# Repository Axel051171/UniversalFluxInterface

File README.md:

<!-- boardrepo-badge:v1 -->

<!-- /boardrepo-badge:v1 -->

# UFI – Universal Flux Interface (Headless)

Flux-Lese-/Schreibgerät für Disketten: STM32H723 (550 MHz) misst jede Flusswechsel-Zeit mit
275 MHz (3,6 ns) und streamt sie per USB an den PC. Kein Raspberry Pi, kein Betriebssystem auf
dem Gerät – das frühere CM5-/Modul-Konzept ist aufgegeben (steht in der Git-Historie).

| | |
|---|---|
| MCU | STM32H723ZGT6, 550 MHz |
| Auflösung | 275 MHz Timer-Capture (3,6 ns), Index auf derselben Zeitbasis |
| Puffer | 8 MB QSPI-PSRAM (Ringpuffer beim Streamen, bis 200 Umdrehungen) |
| USB | USB-C, Full Speed, Datenstrom ~2 Byte je Flusswechsel, sendet während die Diskette dreht |
| Laufwerke | 34-pol PC/Shugart (DENSITY, DRATE, bis 4 Laufwerke), Amiga DB23 (Header, 2 Laufwerke), Apple Disk II (20-pol, 2 Laufwerke), Commodore IEC (1541) |
| Schreiben | Timer + DMA, Precompensation, Verify; Schreibsperre in Hardware (Frontschalter SCHREIBEN + Firmware-Freigabe) |
| Platine v1.0 | 110 × 97 mm, 6 Lagen, für ein geschlossenes Gehäuse (von außen nur USB-C und LAN): eFuses für 5 V/12 V der Laufwerke mit Strommessung, MOSFET-Bustreiber, 4 GB SD-NAND, TCXO, RTC mit CR2032, SHT40, W5500-LAN, Apple-Disk-II- und Mac-3,5"-Port, Sync-Sensor-Eingang, Front-Header J12 |
| Ohne PC | Taster: ganze Diskette als SCP auf den internen Speicher (mit Qualitätsbericht) oder Disk-zu-Disk-Kopie, danach als USB-Laufwerk am PC abholen |
| Greaseweazle-kompatibel | `UFI.CFG protocol=gw`: die Greaseweazle-Werkzeuge (`gw read`, `gw write`, …) erkennen das Board direkt |
| USB-Floppy | Betriebsart-Schalter: PC-Disketten (360K–2,88 MB, DMF) erscheinen am PC als normales USB-Diskettenlaufwerk, ohne Treiber; Atari ST, Commodore 1581 und Amiga 880K als Block-Laufwerk (Sektorabbild wie ST/D81/ADF) |

## Aufbau des Repos

| Ordner | Inhalt |
|---|---|
| [`kicad/UFI_Headless/`](kicad/UFI_Headless/README.md) | Schaltplan, Layout, Fertigungsdaten (`fertigung/`), Build- und ECO-Skripte |
| [`kicad/C64_PSU_Guard/`](kicad/C64_PSU_Guard/README.md) | Eigenständige Schutzplatine: 5 V / 12 V aus einem PC-Netzteil für ein 1541-II / 1581 (eFuse, Verpolschutz, Fehler-LEDs), JLC-Fertigungsdaten |
| [`firmware/`](firmware/) | STM32H723-Firmware (CMake, STM32Cube HAL) |
| [`software/ufi_host/`](software/ufi_host/README.md) | Python-Host (`ufi`): Lesen/Schreiben, SCP-Export, Protokollbeschreibung |
| [`docs/`](docs/README.md) | USB-Protokoll, Umsetzungsstand und Nachweise der Firmware, Speicheraufteilung, Abnahmepläne, Vergleiche mit fremder Floppy-Firmware, Amiga-DB23-Adapterkabel |

## Firmware bauen

```bash
cmake -S firmware -B firmware/build -G Ninja
cmake --build firmware/build        # -> ufi_firmware.bin
```

Erwartet arm-none-eabi-gcc und STM32Cube H7 V1.11.0 unter `~/STM32Cube/Repository/STM32Cube_FW_H7_V1.11.0`
(Pfad in `firmware/CMakeLists.txt`).

Flashen per SWD oder USB-DFU (Taster A beim Einschalten halten bzw. `ufi bootloader`).

## Prüfen ohne Hardware

```bash
pip install -r requirements-test.txt     # pytest, pyserial, py65 (festgelegte Versionen)
python firmware/tests/check_all.py       # native Tests, Firmware-Regressionen, Host-Tests, 6502-Laufwerkscode
```

Braucht clang oder gcc. Die externen Referenzkorpora werden ohne Download übersprungen
(`python firmware/tests/test_flux_corpus.py --download`, ebenso `test_gcr_corpus.py`,
`test_hfe_v3_reference.py`); mit `--require-corpora` schlägt der Lauf ohne sie fehl.
Ergebnis in `firmware/tests/build/offline_gate.json`. Weitere Schritte der CI:
`firmware/tools/check_static.py` (Clang-Analyse, 34 Module, HAL-gebundene gegen `firmware/tests/hal_stub/`),
`firmware/tests/run_fuzz.py` (LibFuzzer: Dateiparser, der komplette v2-Dispatcher, das Greaseweazle-Protokoll
das SD-Modul mit Bildladern, Dump-Writern und UFI.CFG über ein In-Memory-FatFs und die Laufwerkssteuerung
gegen ein Kopfmodell mit TRK00-Sensor, alles hinter erzeugten Treiber-Stubs, `--target v2|gw|sd|drive`).
`python firmware/tests/coverage.py` misst mit clang/llvm-cov, welche Zeilen und Zweige der nativ
gebauten Firmware-Module die Tests erreichen (`firmware/tests/build/coverage.txt`, `cov/html/`).

## Status

Platine v1.0 ist zur Fertigung freigegeben (Tag `hw-v1.0`: ERC 0/0, DRC 0/0/0 mit Schaltplan-Parität, Lastpfade geprüft, JLC-Daten in `kicad/UFI_Headless/fertigung/`) – [Freigabebericht](kicad/UFI_Headless/docs/Freigabe_v1.0.md), [Bestell-Anleitung JLC](kicad/UFI_Headless/docs/Bestellung_JLC.md). Die LAN-Firmware fehlt noch; bis dahin bleibt der W5500 im Reset.
Firmware 1.18-dev: Umfang und Nachweise in [docs/Implementation_Status.md](docs/Implementation_Status.md) und
[docs/Firmware_Erweiterungen_2026-10-16.md](docs/Firmware_Erweiterungen_2026-10-16.md), Schnittstelle in [docs/USB_Protokoll.md](docs/USB_Protokoll.md).
Hardware und Firmware sind noch nicht am echten Gerät getestet – Ablauf für den Prototyp: [Inbetriebnahme-Checkliste](kicad/UFI_Headless/docs/Inbetriebnahme.md),
Schreibpfad: [Abnahme](docs/Abnahme_Schreibpfad.md).

Lizenz: siehe [LICENSE](LICENSE).

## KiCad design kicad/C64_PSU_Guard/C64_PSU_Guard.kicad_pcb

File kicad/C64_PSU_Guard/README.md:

# C64 PSU Guard – geschützte 5 V / 12 V für ein 1541-II / 1581 aus einem PC-Netzteil

Status: **Schaltplan + Layout v0.2** (2026-10-26, Review vom 2026-10-24 umgesetzt), ERC 0/0, DRC 0/0/0, Lastpfade mit `check_routing.py` gemessen (2 Lagen, 58 × 44 mm, JLCPCB-Bestückung), **noch nicht gebaut**.

Änderungen v0.1 → v0.2: J1 und J3 verpolsichere JST-XH-Stecker (B4B-XH-A) statt Stiftleisten, D6 SMAJ13A (unidirektional) statt SMAJ15CA, 100k-Pull-ups R20/R21 an FLT5/FLT12, Lastpfade durchgehend 1,0 mm (v0.1: Zwischenknoten V5_P/V12_P nur 0,25 mm, weil das Netzklassen-Muster den Blattpräfix `/` nicht traf), J3 1:1 auf UFI v1.0 J20 GUARD.

Eigenständige Platine, unabhängig vom UFI-Board. Sie sitzt zwischen dem internen PC-Netzteil des Geräts und dem 4-poligen DIN-Stromanschluss des Commodore-Laufwerks (Original-Netzteil DV-5128UP: 5 V 700 mA, 12 V 500 mA) und ersetzt dessen Schutzfunktion. Ein PC-Netzteil liefert auf beiden Schienen viele Ampere, ohne Begrenzung würde ein Kurzschluss im Laufwerk das dünne DIN-Kabel und die Laufwerksplatine beschädigen.

Klemme J2 mit Ersatzmodell (Phoenix MKDS, gleiche Bauform) zur Kontrolle der Drahtöffnungen: `docs/j2_terminal_standin.png` (`scripts/render_j2_standin.py`).

## Was die Platine erkennt und tut

Zwei gleiche Kanäle (5 V und 12 V), je:

| Block | Teile | Verhalten |
|---|---|---|
| Verpolschutz | AO3401A als ideale Diode (Q1/Q3), Gate über 100k an GND, BZT52C10 klemmt Vgs | negative Eingangsspannung: Kanal bleibt stromlos, LED **REV POL** (D9) leuchtet (über 1N4148W D10/D11 von der negativen Schiene gespeist) |
| Eingangsschutz | SMF5.0CA (5 V, bidirektional) / SMAJ13A (12 V, unidirektional, Kathode an V12_P), 10 µF + 100 nF | Spannungsspitzen vom Netzteil; SMAJ13A: V_RWM 13 V, V_BR 14,4–15,9 V bei 1 mA, V_C 21,5 V bei 18,6 A (Vishay-Tabelle SMAJ13A, JLC-Daten Diodes SMAJ13A-13-F gleich, I_R ≤ 5 µA) – unter dem 22-V-Kurzzeitwert (≤ 10 ms) des TPS25921A; der SMAJ15CA aus v0.1 klemmte erst bei 24,4 V |
| eFuse | TPS25921ADR (U1/U2), SOIC-8 | Strombegrenzung, Schnellabschaltung in 3 µs, Über-/Unterspannung über Teiler, Sanftanlauf 22 nF, thermischer Schutz, **Auto-Retry** |
| Anzeige | grün am Ausgang (**5V OK** D3, **12V OK** D7), rot am FLT-Pin (**5V ERR** D4, **12V ERR** D8), FLT zusätzlich mit 100k (R20/R21) auf V5_P/V12_P | rot = FLT aktiv: Über-/Unterspannung, ENUV aus (OFF) oder thermische Abschaltung; erlischt, sobald der Fehler weg ist. **Während der reinen Strombegrenzung bleibt Rot aus** (FLT meldet sie nicht), Rot kommt erst mit der thermischen Abschaltung (Kurzschluss: blinkt im Takt Abschaltung / Retry) |
| UFI-Anschluss | J3 (JST XH) für UFI J20, 2N7002 (Q2/Q4) ziehen ENUV nach GND | Pin 2 OFF high = beide Kanäle aus; ERR-Ausgänge open drain über Q5/Q6 (Pull-up auf der UFI-Seite) |

Dimensionierung (TPS25921A: I_LIMIT ≈ 0,0105 A/kΩ, Schnellabschaltung 0,0142 A/kΩ + 0,36 A, Schwellen ENUV/OVP 1,39 V steigend / 1,34 V fallend):

| | 5-V-Kanal | 12-V-Kanal |
|---|---|---|
| Strombegrenzung (R_ILIM) | 1,21 A (R6 115k), Schnellabschaltung 2,0 A | 1,50 A (R14 143k), Schnellabschaltung 2,4 A |
| Überspannung aus / wieder ein | 6,0 V / 5,8 V (R4 100k, R5 30k) | 14,0 V / 13,5 V (R12 100k, R13 11k) |
| Unterspannung ein / aus | 4,18 V / 4,03 V (R2 100k, R3 49,9k) | 10,4 V / 10,0 V (R10 100k, R11 15,4k) |
| Anlaufzeit (C_SS 22 nF) | ≈ 23 ms | ≈ 54 ms |
| LED-Vorwiderstände | 1k (≈ 3 mA) | 3,3k (≈ 3 mA) |

Die Anlaufzeit hält den Einschaltstrom in die Elkos des Laufwerks unter der Begrenzung (2200 µF an 5 V ergeben ≈ 0,5 A). Der Motoranlauf des 1541-II liegt unter 1 A und wird nicht begrenzt.

**Was die Platine nicht sehen kann:** einen falsch belegten DIN-Stecker am Laufwerksende. Die Kabelbelegung einmal mit dem Multimeter prüfen (unten).

## Anschlüsse

| Stecker | Belegung |
|---|---|
| J1 PSU IN (JST XH B4B-XH-A, 2,5 mm, verpolsicher, LCSC C144395) | 1 +5 V (rot), 2 und 3 GND (schwarz), 4 +12 V (gelb) = Belegung des kleinen Floppy-Stromsteckers (Berg) eines PC-Netzteils; Anschluss über das Adapterkabel Berg → XH (unten). Pin 1 = eckiges Pad, oben. Wie UFI J17/J3 (v1.0) |
| J2 DRIVE (Schraubklemme 3-polig, 5 mm, Drahtöffnungen zur Platinenkante) | 1 +5 V → DIN Pin 1, 2 GND → DIN Pin 2, 3 +12 V → DIN Pin 4; DIN Pin 3 bleibt frei. Auf der Platine von oben nach unten 12 V, GND, 5 V, Beschriftung neben den Klemmen |
| J3 UFI (JST XH B4B-XH-A, LCSC C144395) | 1 GND, 2 OFF (high = beide Kanäle aus, 100k Pull-down), 3 ERR5, 4 ERR12 (open drain über Q5/Q6: low = Kanal an, high = Kanal abgeschaltet oder Platine stromlos); unbeschaltet lassen = normaler Betrieb. Gleiche Pinfolge wie UFI J20, 1:1-Kabel |
| J4 EXT ERR (Stiftleiste 1×2) | eine externe Fehler-LED: 1 = Anode (+), 2 = Kathode (−), Vorwiderstand R19 ist auf der Platine (≈ 2,5 mA). Leuchtet, solange der 5-V- oder der 12-V-Kanal abgeschaltet ist (Dioden-ODER D12/D13 auf die FLT-Ausgänge). Verpolung zeigt nur die Platinen-LED REV POL, weil die eFuses dann stromlos sind |
| H1–H4 | M3, mit GND verbunden |

DIN-Stecker am Laufwerkskabel (Blick auf die Stiftseite des Steckers, Nase unten, wie auf dem Netzteil-Label): oben links 3 (frei), oben rechts 2 GND, unten links 4 +12 V, unten rechts 1 +5 V. Vor dem ersten Einschalten mit dem Multimeter zwischen Schraubklemme und Steckerstiften durchklingeln.

## Anschluss an das UFI-Board (v1.0)

J3 ↔ **J20 GUARD** des UFI Headless v1.0 (Blatt MCU_Core), beide JST XH B4B-XH-A, Kabel **1:1** (zwei XHP-4-Gehäuse, SXH-001T-P0.6, AWG 24–22, Pin 1 auf Pin 1). Belegung aus der UFI-Netzliste (`kicad-cli sch export netlist`, 2026-10-26); Firmware-Unterstützung gibt es noch nicht:

| Guard J3 | UFI J20 | UFI-Seite | Richtung / Pegel |
|---|---|---|---|
| 1 GND | 1 GND | – | |
| 2 OFF | 2 GUARD_OFF_J | R125 220 Ω → PG7, PESD3V3L1BA D32 | UFI → Guard: GPIO-Ausgang 3,3 V, high = beide Kanäle aus. Guard: 100k Pull-down R18, Gates von Q2/Q4 (2N7002, V_GS(th) ≤ 2,5 V laut JLC-Daten) – 3,3 V schalten sicher, Gate-Last rein kapazitiv |
| 3 ERR5 | 3 GUARD_ERR5_J | R126 220 Ω → PG8, 10k Pull-up R107 auf +3V3, PESD3V3L1BA D33 | Guard → UFI: open drain (Q5), low = 5-V-Kanal an, high (Pull-up) = Kanal aus oder Guard stromlos |
| 4 ERR12 | 4 GUARD_ERR12_J | R127 220 Ω → PC9, 10k Pull-up R108 auf +3V3, PESD3V3L1BA D34 | wie ERR5 (Q6) |

Pegel geprüft: Die Guard-Drains sehen nur die 3,3 V der UFI-Pull-ups (kein Guard-eigener Pull-up), die FLT-Knoten (bis 12 V) erreichen J3 nicht, sie steuern nur die Gates von Q5/Q6 (V_GS max. ±20 V). Low-Pegel an PG8/PC9: 10k gegen R_DS(on) des 2N7002 (≤ 5 Ω bei 10 V, bei 5 V Gate höher, aber ≪ 10k) → deutlich unter 0,3 V. Keine Pegel- oder Richtungsabweichung gefunden. Ohne UFI-Kabel: OFF über R18 low (Kanäle an), ERR-Ausgänge offen.

Die FLT-Pins der eFuses liegen ohne Fehler auf Schienenspannung (über R20/R21 100k und die rote LED-Kette), deshalb gehen sie nicht direkt auf J3, sondern über die Inverter Q5/Q6.

## Inbetriebnahme

### Adapterkabel (ab v0.2)

J1 ist ein JST-XH-Stecker (B4B-XH-A, 2,5 mm), das XH-Gehäuse passt nur in einer Lage – wie J17/J3 am UFI v1.0 (`kicad/UFI_Headless/docs/Inbetriebnahme.md`, Abschnitt „Kabel für v1.0“). Kabel jeweils mit XH-Buchsengehäuse XHP-4 und Crimpkontakten SXH-001T-P0.6, AWG 22:

| Kabel | Guard-Seite | andere Seite |
|---|---|---|
| PC-Netzteil → J1 | XHP-4: 1 +5 V, 2/3 GND, 4 +12 V | Berg-Buchse (PC-Floppy-Stromstecker) 1:1 nach Pinnummer: 1 rot +5 V, 2/3 schwarz GND, 4 gelb +12 V |
| J3 → UFI J20 | XHP-4, Pin 1–4 | XHP-4 1:1 (Pin 1 auf Pin 1), AWG 24–22 |

Die Berg-Buchse selbst ist nicht kodiert: das Kabel einmal vor dem ersten Stecken mit dem Multimeter prüfen (Netzteil an, XH-Gehäuse: Pin 1 gegen Pin 2 = +5 V, Pin 4 gegen Pin 2 = +12 V). Ein verdrehter Stecker war bei der Stiftleiste von v0.1 nicht ausgeschlossen und hätte 12 V auf den 5-V-Kanal gelegt (Q1 leitet, D2 SMF5.0CA brennt durch).

### Schritte

1. Adapterkabel wie oben prüfen. Platine ohne Laufwerk ans Netzteil: beide grünen LEDs an, keine rote. Ausgänge messen: 5,0 V und 12,0 V.
2. Kodierung prüfen: Der XH-Stecker lässt sich nicht verdreht aufstecken – nicht mit Gewalt versuchen. (Der v0.1-Test „J1 um 180° verdreht“ entfällt: er setzt den 5-V-Kanal 12 V aus, D2 ist ein 5-V-TVS.)
3. Strombegrenzung 5 V: Ausgang mit einem **2,2-Ω-Widerstand ≥ 5 W** belasten (in der Begrenzung 1,21 A × 2,7 V ≈ 3,2 W im Widerstand, der eFuse U1 trägt ≈ 2,8 W). Erwartet: Ausgang fällt auf ≈ 2,7 V, die **grüne LED bleibt schwach an**, die **rote LED bleibt während der Begrenzung aus** (FLT meldet keine Strombegrenzung). Erst wenn U1 thermisch abschaltet, leuchtet **5V ERR**, danach Auto-Retry (Rot/Grün wechseln). Beim Zuschalten an den laufenden Ausgang kann die Schnellabschaltung (2,0 A) einmal kurz ansprechen. Widerstand weg, Kanal kommt von selbst zurück.
4. Laufwerk anschließen, Diskette lesen, dabei die 12 V am Ausgang beobachten (Motoranlauf darf die rote LED nicht auslösen).
5. Mit UFI-Kabel an J20: OFF (PG7) high → beide grünen LEDs aus, beide roten an, ERR5/ERR12 am UFI high; OFF low → alles wieder an, ERR5/ERR12 low.

## Fertigung (JLCPCB)

`fertigung/`: Gerber und Bohrdaten in `gerber/` (das Upload-ZIP erzeugt `scripts/make_fab.sh`; ZIP-Dateien sind nicht versioniert), `C64_PSU_Guard-bom-jlc.csv`, `C64_PSU_Guard-cpl-jlc.csv`, `JLC_Rotation_Check.md` (Pin-1-Kontrolle im Bestückungsviewer), `erc.rpt`/`drc.rpt` (nach der letzten Boardänderung erzeugt), `check_routing.txt`. 2 Lagen, 1,6 mm, Leiterbahnen ≥ 0,25 mm, Lastnetze (Netzklasse `Load`) 1,0 mm, gemessen mit `check_routing.py` gegen `routing_rules.json`. Alle LCSC-Nummern stehen im Schaltplan (`LCSC`-Feld), Lager am 2026-10-26 über die JLC-API geprüft: TPS25921ADR C189199 **nur 681 Stück** (Extended), SMAJ13A-13-F C110519 12 552, B4B-XH-A C144395 708 952, 100k C25803 18 Mio. (Basic), übrige Positionen unverändert lagernd.

**Lastpfade (v0.2, gemessen):** J1 → Q → TVS → 10 µF → 100 nF → U(IN) und U(OUT) → 1 µF → J2 sind vorgeroutet (gesperrt, F.Cu, 1,0 mm); nur +5V_OUT wechselt hinter C4 über ein Via-Paar (0,8/0,4 mm) auf B.Cu zur Klemme. Längen und Widerstände pro Abschnitt in `fertigung/check_routing.txt`. Freerouting führt die Abzweige der Lastnetze (Teiler, LED- und Pull-up-Widerstände, Zener, REV-Dioden, ≤ 3 mA) ebenfalls mit 1,0 mm, dort teils mit einem einzelnen Via.

## Werkzeugweg

Wie beim UFI-Board: Schaltplan und Layout entstehen aus Skripten, die Dateien in KiCad sind das Ergebnis.

```bash
# Schaltplan -> ERC -> Netzliste -> Platzierung -> Freerouting -> GND-Flächen -> DRC
TOOLS=/pfad/zu/freerouting-2.4.1.jar+jdk-25-jre bash scripts/make_pcb.sh
# Gerber, BOM, CPL, Vorschaubilder
bash scripts/make_fab.sh
```

`scripts/build_schematic.py` (Bauteile, Netze, LCSC), `scripts/build_pcb.py` (Platzierung, Umriss, Bestückungsdruck), `scripts/finish_pcb.py` (GND-Flächen beidseitig, Via neben jedem SMD-GND-Pad). Freerouting 2.4.1 braucht Java 25. Projektbibliothek `lib/C64_PSU_Guard.kicad_sym` enthält das TPS25921-Symbol. Der MaiXu-Klemmen-Footprint hat in KiCad 10 kein 3D-Modell, J2 fehlt daher im Rendering; die Lage der Drahtöffnungen wurde mit dem Phoenix-MKDS-Modell desselben Footprint-Generators geprüft.

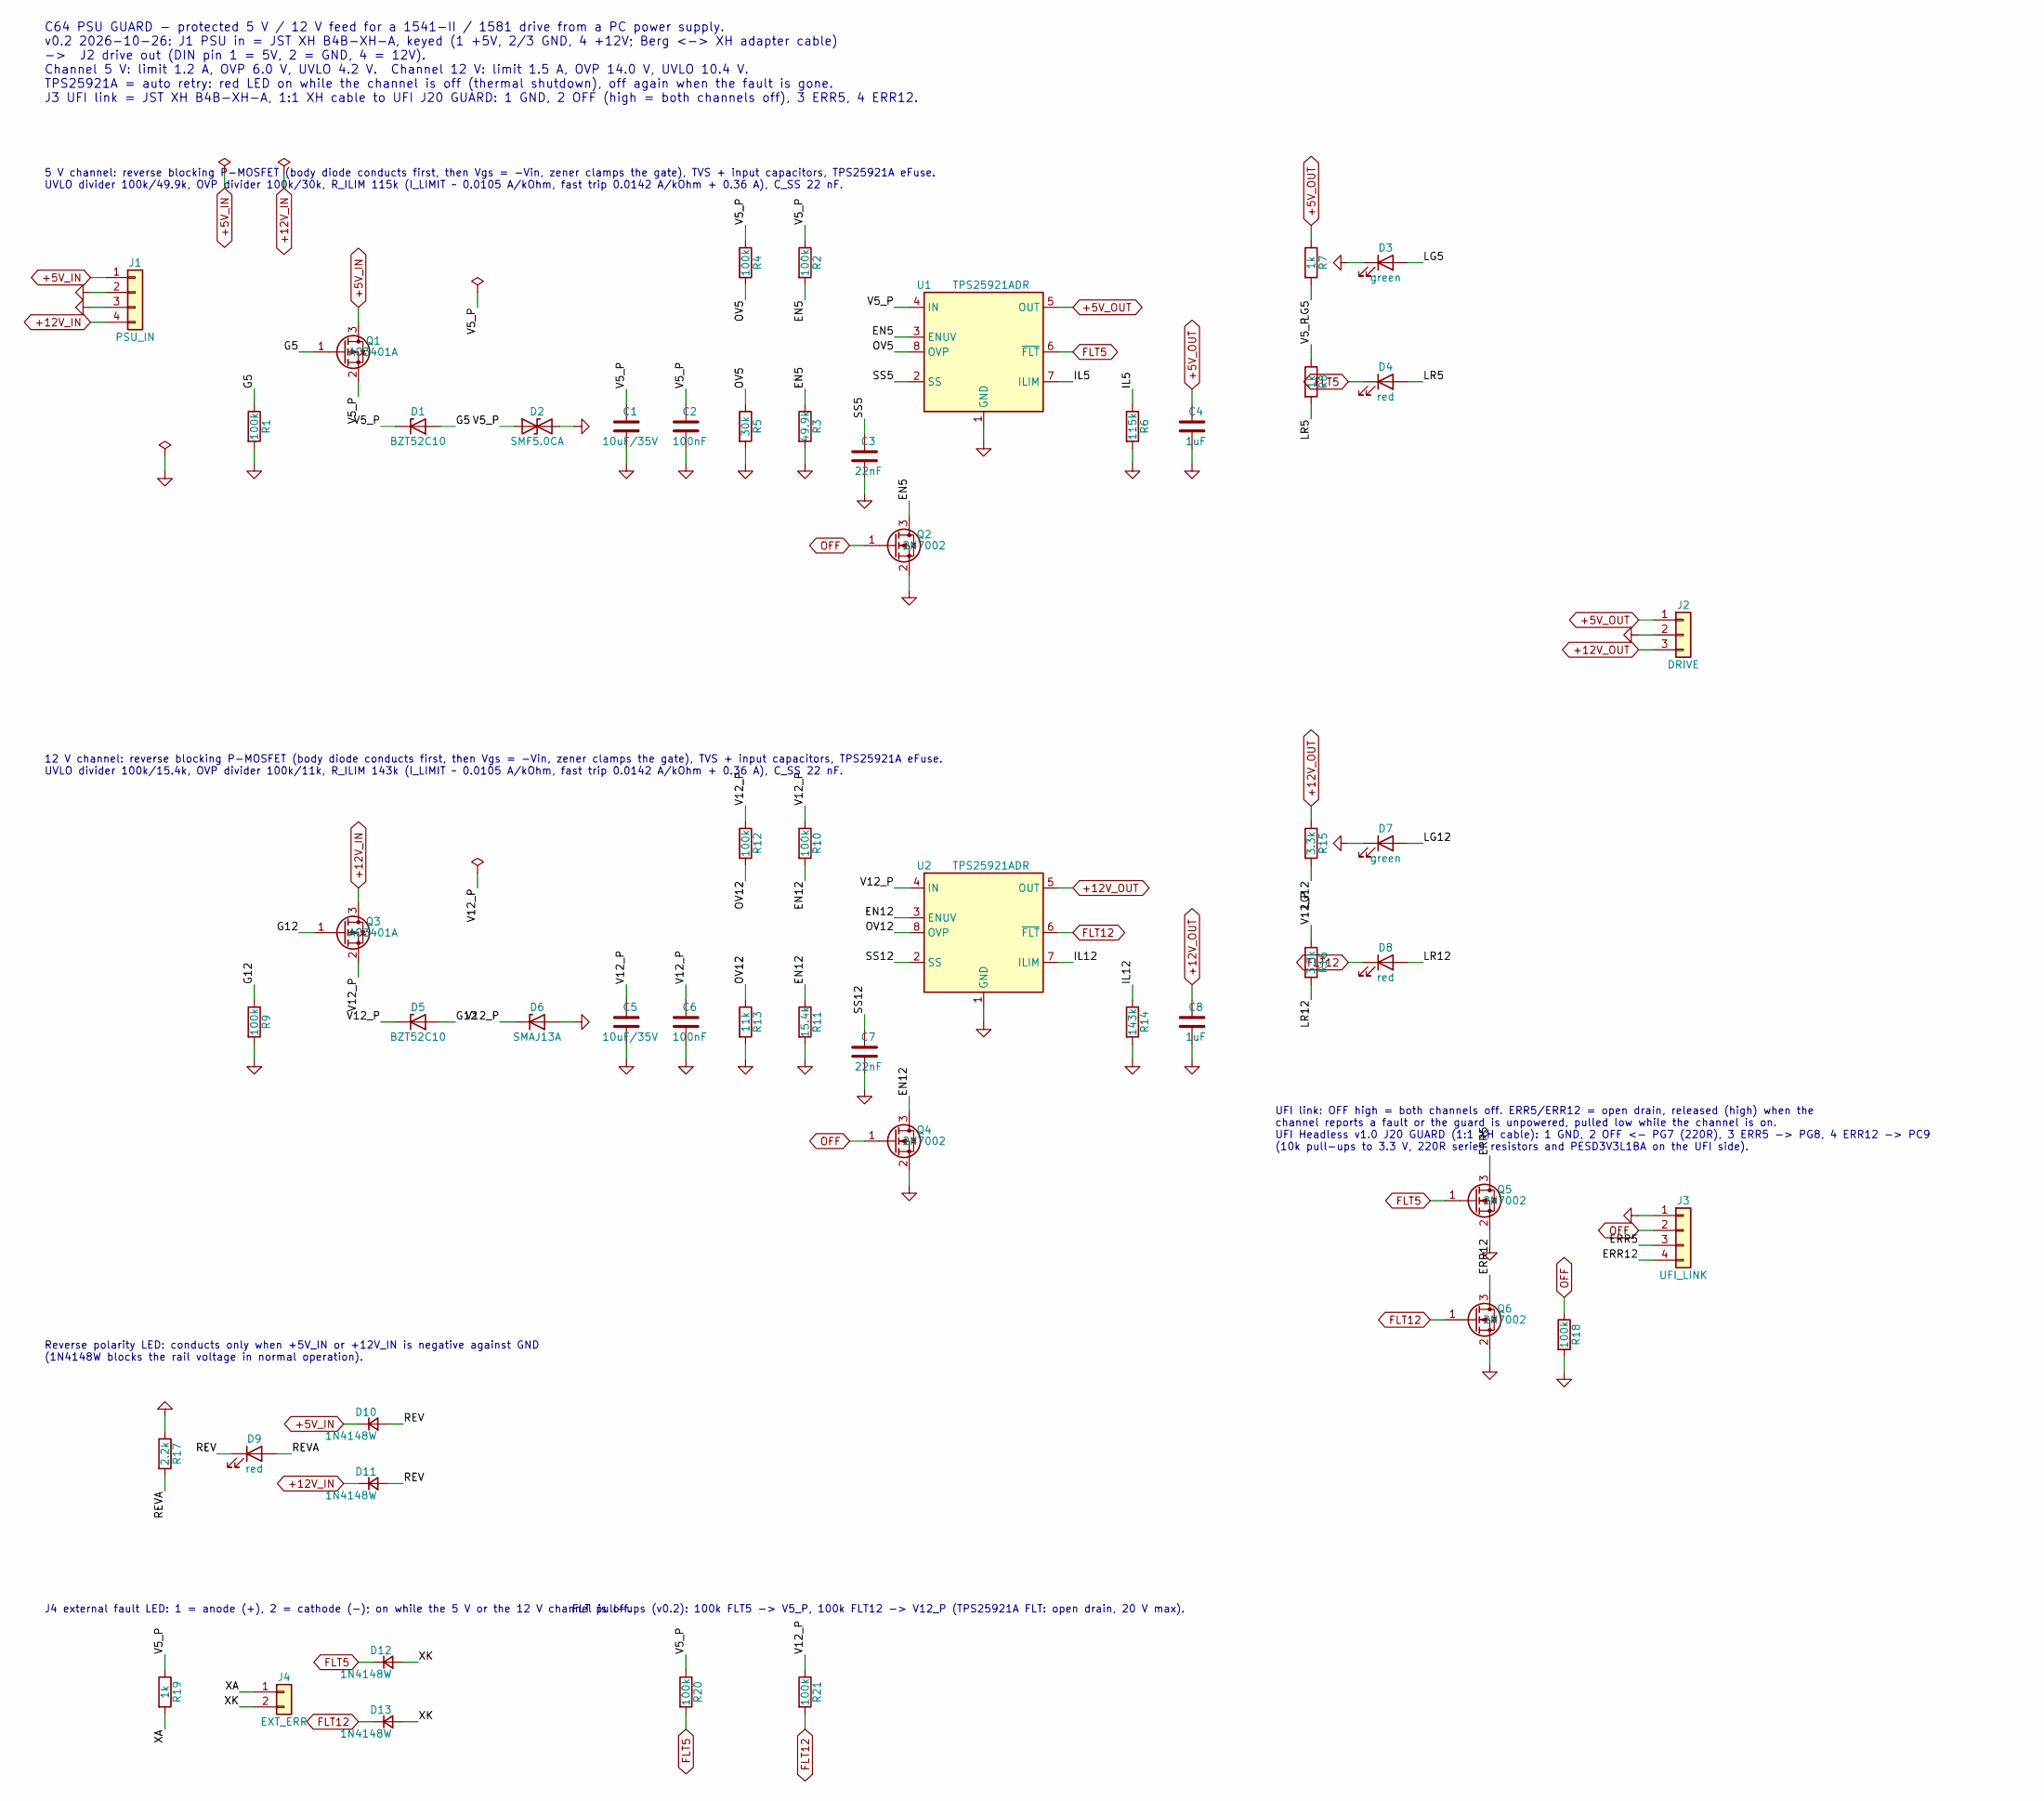
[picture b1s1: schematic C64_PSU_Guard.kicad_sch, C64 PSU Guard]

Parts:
C1, C5: 10uF/35V; C_1206_3216Metric; LCSC C454102
C2, C6: 100nF; C_0603_1608Metric; LCSC C14663
C3, C7: 22nF; C_0603_1608Metric; LCSC C21122
C4, C8: 1uF; C_0603_1608Metric; LCSC C15849
D1, D5: BZT52C10; D_SOD-123; LCSC C2103
D2: SMF5.0CA; D_SMF; LCSC C2980402
D3, D7: green; LED_0603_1608Metric; LCSC C12624
D4, D8, D9: red; LED_0603_1608Metric; LCSC C2286
D6: SMAJ13A; D_SMA; MPN Diodes SMAJ13A-13-F (unidirectional TVS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; LCSC C110519
D10, D11, D12, D13: 1N4148W; D_SOD-123; LCSC C81598
J1: PSU_IN; JST_XH_B4B-XH-A_1x04_P2.50mm_Vertical; MPN JST B4B-XH-A(LF)(SN) (XH 2.5 mm, 3 A, k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; LCSC C144395
J2: DRIVE; TerminalBlock_MaiXu_MX126-5.0-03P_1x03_P5.00mm; LCSC C474882
J3: UFI_LINK; JST_XH_B4B-XH-A_1x04_P2.50mm_Vertical; MPN JST B4B-XH-A(LF)(SN) (XH 2.5 mm, 3 A, k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; LCSC C144395
J4: EXT_ERR; PinHeader_1x02_P2.54mm_Vertical; LCSC C54620389
Q1, Q3: AO3401A; SOT-23; LCSC C15127
Q2, Q4, Q5, Q6: 2N7002; SOT-23; LCSC C8545
R1, R2, R4, R9, R10, R12, R18, R20, R21: 100k; R_0603_1608Metric; LCSC C25803
R3: 49.9k; R_0603_1608Metric; LCSC C23184
R5: 30k; R_0603_1608Metric; LCSC C22984
R6: 115k; R_0603_1608Metric; LCSC C22783
R7, R8, R19: 1k; R_0603_1608Metric; LCSC C21190
R11: 15.4k; R_0603_1608Metric; LCSC C22804
R13: 11k; R_0603_1608Metric; LCSC C25950
R14: 143k; R_0603_1608Metric; LCSC C22877
R15, R16: 3.3k; R_0603_1608Metric; LCSC C22978
R17: 2.2k; R_0603_1608Metric; LCSC C4190
U1, U2: TPS25921ADR; SOIC-8_3.9x4.9mm_P1.27mm; MPN TPS25921ADR; LCSC C189199

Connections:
+5V_IN: D10.1 (K), J1.1, Q1.3 (D)
+5V_OUT: C4.1, J2.1, R7.1, U1.5 (OUT)
+12V_IN: D11.1 (K), J1.4, Q3.3 (D)
+12V_OUT: C8.1, J2.3, R15.1, U2.5 (OUT)
/EN5: Q2.3 (D), R2.2, R3.1, U1.3 (ENUV)
/EN12: Q4.3 (D), R10.2, R11.1, U2.3 (ENUV)
/ERR5: J3.3, Q5.3 (D)
/ERR12: J3.4, Q6.3 (D)
/G5: D1.2 (A), Q1.1 (G), R1.1
/G12: D5.2 (A), Q3.1 (G), R9.1
/IL5: R6.1, U1.7 (ILIM)
/IL12: R14.1, U2.7 (ILIM)
/LG5: D3.2 (A), R7.2
/LG12: D7.2 (A), R15.2
/LR5: D4.2 (A), R8.2
/LR12: D8.2 (A), R16.2
/OV5: R4.2, R5.1, U1.8 (OVP)
/OV12: R12.2, R13.1, U2.8 (OVP)
/REV: D9.1 (K), D10.2 (A), D11.2 (A)
/REVA: D9.2 (A), R17.2
/SS5: C3.1, U1.2 (SS)
/SS12: C7.1, U2.2 (SS)
/V5_P: C1.1, C2.1, D1.1 (K), D2.1 (A1), Q1.2 (S), R2.1, R4.1, R8.1, R19.1, R20.1, U1.4 (IN)
/V12_P: C5.1, C6.1, D5.1 (K), D6.1 (K), Q3.2 (S), R10.1, R12.1, R16.1, R21.1, U2.4 (IN)
/XA: J4.1, R19.2
/XK: D12.2 (A), D13.2 (A), J4.2
FLT5: D4.1 (K), D12.1 (K), Q5.1 (G), R20.2, U1.6 (~FLT)
FLT12: D8.1 (K), D13.1 (K), Q6.1 (G), R21.2, U2.6 (~FLT)
GND: C1.2, C2.2, C3.2, C4.2, C5.2, C6.2, C7.2, C8.2, D2.2 (A2), D3.1 (K), D6.2 (A), D7.1 (K), J1.2, J1.3, J2.2, J3.1, Q2.2 (S), Q4.2 (S), Q5.2 (S), Q6.2 (S), R1.2, R3.2, R5.2, R6.2, R9.2, R11.2, R13.2, R14.2, R17.1, R18.2, U1.1 (GND), U2.1 (GND); also elsewhere on the board
OFF: J3.2, Q2.1 (G), Q4.1 (G), R18.1

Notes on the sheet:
C64 PSU GUARD - protected 5 V / 12 V feed for a 1541-II / 1581 drive from a PC power supply. v0.2 2026-10-26: J1 PSU in = JST XH B4B-XH-A, keyed (1 +5V, 2/3 GND, 4 +12V; Berg <-> XH adapter cable) -> J2 drive out (DIN pin 1 = 5V, 2 = GND, 4 = 12V). Channel 5 V: limit 1.2 A, OVP 6.0 V, UVLO 4.2 V. C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
5 V channel: reverse blocking P-MOSFET (body diode conducts first, then Vgs = -Vin, zener clamps the gate), TVS + input capacitors, TPS25921A eFuse. UVLO divider 100k/49.9k, OVP divider 100k/30k, R_ILIM 115k (I_LIMIT ~ 0.0105 A/kOhm, fast trip 0.0142 A/kOhm + 0.36 A), C_SS 22 nF.
12 V channel: reverse blocking P-MOSFET (body diode conducts first, then Vgs = -Vin, zener clamps the gate), TVS + input capacitors, TPS25921A eFuse. UVLO divider 100k/15.4k, OVP divider 100k/11k, R_ILIM 143k (I_LIMIT ~ 0.0105 A/kOhm, fast trip 0.0142 A/kOhm + 0.36 A), C_SS 22 nF.
Reverse polarity LED: conducts only when +5V_IN or +12V_IN is negative against GND (1N4148W blocks the rail voltage in normal operation).
UFI link: OFF high = both channels off. ERR5/ERR12 = open drain, released (high) when the channel reports a fault or the guard is unpowered, pulled low while the channel is on. UFI Headless v1.0 J20 GUARD (1:1 XH cable): 1 GND, 2 OFF <- PG7 (220R), 3 ERR5 -> PG8, 4 ERR12 -> PC9 (10k pull-ups to 3.3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
J4 external fault LED: 1 = anode (+), 2 = cathode (-); on while the 5 V or the 12 V channel is off.
FLT pull-ups (v0.2): 100k FLT5 -> V5_P, 100k FLT12 -> V12_P (TPS25921A FLT: open drain, 20 V max).

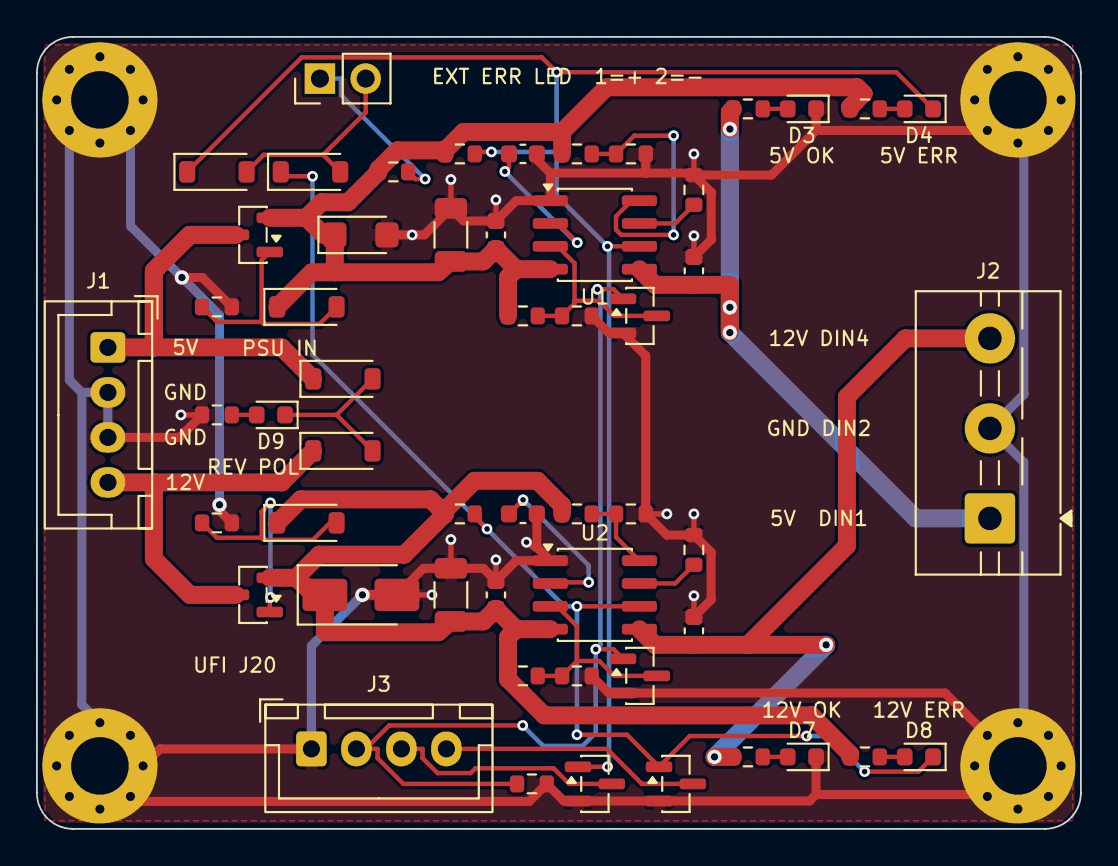
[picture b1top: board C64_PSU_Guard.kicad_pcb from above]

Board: 2 copper layers, 58.0 x 44.0 mm, 58 parts (0 on the bottom side), 30 nets.

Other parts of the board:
H1, H2, H3, H4: M3; MountingHole_3.2mm_M3_Pad_Via

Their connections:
GND: H1.1, H2.1, H3.1, H4.1; also elsewhere on the board

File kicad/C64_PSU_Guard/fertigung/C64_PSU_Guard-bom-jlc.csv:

"Comment","Designator","Footprint","LCSC Part #"
"10uF/35V","C1,C5","Capacitor_SMD:C_1206_3216Metric","C454102"
"100nF","C2,C6","Capacitor_SMD:C_0603_1608Metric","C14663"
"22nF","C3,C7","Capacitor_SMD:C_0603_1608Metric","C21122"
"1uF","C4,C8","Capacitor_SMD:C_0603_1608Metric","C15849"
"BZT52C10","D1,D5","Diode_SMD:D_SOD-123","C2103"
"SMF5.0CA","D2","Diode_SMD:D_SMF","C2980402"
"green","D3,D7","LED_SMD:LED_0603_1608Metric","C12624"
"red","D4,D8,D9","LED_SMD:LED_0603_1608Metric","C2286"
"SMAJ13A","D6","Diode_SMD:D_SMA","C110519"
"1N4148W","D10-D13","Diode_SMD:D_SOD-123","C81598"
"PSU_IN","J1","Connector_JST:JST_XH_B4B-XH-A_1x04_P2.50mm_Vertical","C144395"
"DRIVE","J2","TerminalBlock:TerminalBlock_MaiXu_MX126-5.0-03P_1x03_P5.00mm","C474882"
"UFI_LINK","J3","Connector_JST:JST_XH_B4B-XH-A_1x04_P2.50mm_Vertical","C144395"
"EXT_ERR","J4","Connector_PinHeader_2.54mm:PinHeader_1x02_P2.54mm_Vertical","C54620389"
"AO3401A","Q1,Q3","Package_TO_SOT_SMD:SOT-23","C15127"
"2N7002","Q2,Q4-Q6","Package_TO_SOT_SMD:SOT-23","C8545"
"100k","R1,R2,R4,R9,R10,R12,R18,R20,R21","Resistor_SMD:R_0603_1608Metric","C25803"
"49.9k","R3","Resistor_SMD:R_0603_1608Metric","C23184"
"30k","R5","Resistor_SMD:R_0603_1608Metric","C22984"
"115k","R6","Resistor_SMD:R_0603_1608Metric","C22783"
"1k","R7,R8,R19","Resistor_SMD:R_0603_1608Metric","C21190"
"15.4k","R11","Resistor_SMD:R_0603_1608Metric","C22804"
"11k","R13","Resistor_SMD:R_0603_1608Metric","C25950"
"143k","R14","Resistor_SMD:R_0603_1608Metric","C22877"
"3.3k","R15,R16","Resistor_SMD:R_0603_1608Metric","C22978"
"2.2k","R17","Resistor_SMD:R_0603_1608Metric","C4190"
"TPS25921ADR","U1,U2","Package_SO:SOIC-8_3.9x4.9mm_P1.27mm","C189199"

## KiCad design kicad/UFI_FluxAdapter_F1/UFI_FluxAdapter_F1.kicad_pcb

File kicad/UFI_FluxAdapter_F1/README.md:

# UFI Flux Adapter F1 v1.0

Trägerplatine für ein **STM32F103C8 „Blue Pill“** mit 34-poligem Shugart-Floppy-Anschluss.
Läuft mit der offiziellen **Greaseweazle-F1-Firmware** (Submodell „F1 basic“) und den Greaseweazle-Host-Tools (`gw`).

## Eckdaten

| | |
|---|---|
| Platine | 75 × 54 mm, 2 Lagen, 1,6 mm FR4, GND-Fläche oben und unten |
| Designregeln | Leiterbahn 0,3 mm, Abstand 0,2 mm, Via 0,7/0,35 mm (JLCPCB-Standard reicht) |
| Prüfung | KiCad 10 DRC: 0 Verstöße, 0 unverbundene Pads |
| Bauteile | nur Durchsteck-Steckverbinder, kein SMD-Löten |

## Fertigung

`fertigung/UFI_FluxAdapter_F1_gerber.zip` direkt beim Leiterplattenhersteller hochladen (z. B. JLCPCB).
Standardoptionen genügen: 2 Lagen, 1,6 mm, HASL, beliebige Lötstoppfarbe.

## Stückliste

| Ref | Bauteil | Menge |
|---|---|---|
| J1, J2 | Buchsenleiste 1×20, RM 2,54 mm, gerade | 2 |
| J3 | Wannenstecker (IDC-Box-Header) 2×17, RM 2,54 mm, gerade | 1 |
| – | Blue Pill mit **originalem STM32F103C8T6** (Stiftleisten nach unten eingelötet) | 1 |
| H1–H4 | M3-Abstandsbolzen (optional) | 4 |
| – | 34-poliges Floppy-Flachbandkabel | 1 |

## Anschlussbelegung

Quelle: `greaseweazle-firmware`, `src/mcu/stm32f1/floppy.c` und `board.c`. Die Platine wurde gegen diese Liste automatisch geprüft (`scripts/verify_adapter.py`).

| Floppy-Pin | Signal | Blue Pill |
|---|---|---|
| 2 | DENSEL | PB9 |
| 8 | INDEX | PB6 |
| 10 | Drive Select 0 / Motor A | PB11 |
| 14 | Drive Select 1 | PB10 |
| 18 | DIR | PB12 |
| 20 | STEP | PB13 |
| 22 | WDATA | PB4 |
| 24 | WGATE | PB14 |
| 26 | TRK0 | PB7 |
| 28 | WRPROT | PB8 |
| 30 | RDATA | PB3 |
| 32 | SIDE | PB15 |
| alle ungeraden | GND | GND |
| 4, 6, 12, 16, 34 | – | nicht belegt |

PC14/PC15 bleiben offen, dadurch erkennt die Firmware das Submodell „F1 basic“. Alle genutzten Pins (PB3, PB4, PB6–PB15) sind beim STM32F103 5-V-tolerant, deshalb sind keine Pegelwandler nötig.

## Aufbau

1. Buchsenleisten J1/J2 und Wannenstecker J3 einlöten. Die Lage der Nase am Wannenstecker gibt der Bestückungsdruck vor.
2. Blue Pill einstecken: **Bauteilseite oben, USB-Buchse links**. Die Beschriftungen „VB“ und „3.3“ auf der Trägerplatine müssen neben den gleich beschrifteten Pins der Blue Pill liegen.
3. Floppy-Kabel an J3 anschließen, Pin 1 ist mit ▽ markiert.

## Inbetriebnahme

1. Greaseweazle-F1-Firmware auf die Blue Pill flashen, wie im Greaseweazle-Wiki beschrieben (F1-Firmware-Programmierung).
2. **Das Laufwerk braucht ein eigenes Netzteil** (5 V, bei 5,25"-Laufwerken zusätzlich 12 V). Die USB-Versorgung der Blue Pill reicht dafür nicht. Die Masse des Laufwerks läuft über das Flachbandkabel.
3. Test: `gw info`, danach z. B. `gw read --drive A test.scp` für ein PC-Laufwerk hinter dem Kabeldreh. Die Laufwerksangabe richtet sich nach Kabel und Bustyp, siehe Greaseweazle-Wiki.

Grenze von „F1 basic“: Am IBM-PC-Bus wird nur ein Laufwerk (Unit 0) unterstützt, weil die Pins 12 und 16 nicht belegt sind.

## Reproduzierbarkeit

Das Board wird vollständig von `scripts/build_adapter.py` erzeugt und mit Freerouting geroutet (`scripts/make_adapter.sh`). Das Skript erwartet Java 21 und `freerouting.jar` (v2.1.0) unter `scripts/tools/`; beides ist nicht im Repo enthalten.
`scripts/verify_adapter.py` liest die Netze aus dem fertigen Board zurück und vergleicht sie mit der Firmware-Belegung.
Einen Schaltplan gibt es nicht. Das Board enthält nur Steckverbinder, die Belegung oben ist die vollständige Netzliste.

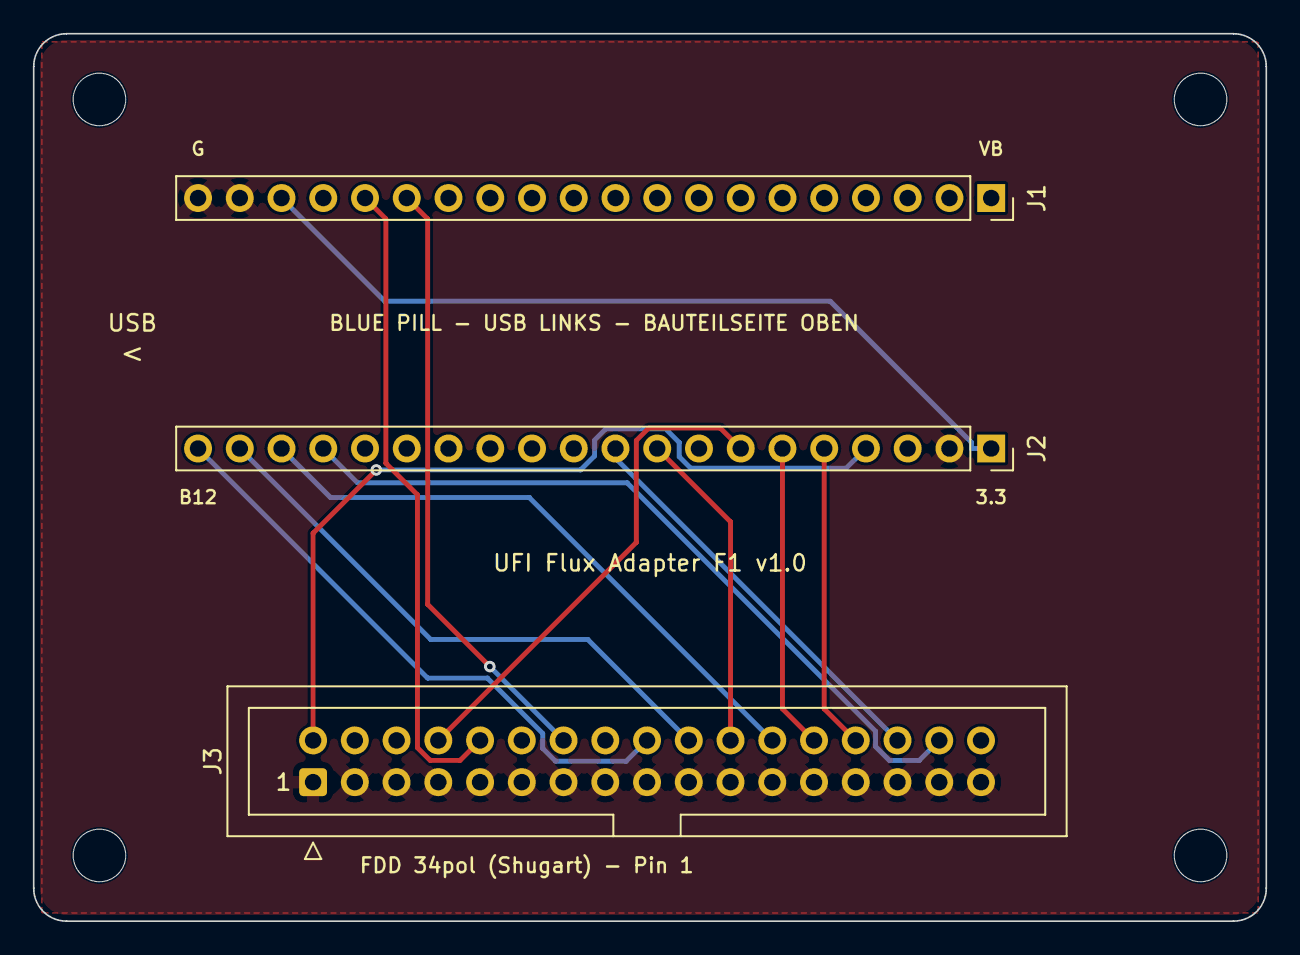
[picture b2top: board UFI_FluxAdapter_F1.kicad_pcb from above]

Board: 2 copper layers, 75.0 x 54.0 mm, 7 parts (0 on the bottom side), 14 nets.

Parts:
H1, H2, H3, H4: M3; MountingHole_3.2mm_M3
J1: BluePill_Top; PinSocket_1x20_P2.54mm_Vertical
J2: BluePill_Bottom; PinSocket_1x20_P2.54mm_Vertical
J3: FDD_34pin; IDC-Header_2x17_P2.54mm_Vertical

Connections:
+3V3: J1.18, J2.1
FDD2_DENSEL: J2.4, J3.2
FDD8_INDEX: J2.7, J3.8
FDD10_SEL0_MOTA: J1.16, J3.10
FDD14_SEL1: J1.15, J3.14
FDD18_DIR: J2.20, J3.18
FDD20_STEP: J2.19, J3.20
FDD22_WDATA: J2.9, J3.22
FDD24_WGATE: J2.18, J3.24
FDD26_TRK0: J2.6, J3.26
FDD28_WRPROT: J2.5, J3.28
FDD30_RDATA: J2.10, J3.30
FDD32_SIDE: J2.17, J3.32
GND: J1.19, J1.20, J2.2, J3.1, J3.3, J3.5, J3.7, J3.9, J3.11, J3.13, J3.15, J3.17, J3.19, J3.21, J3.23, J3.25, J3.27, J3.29, J3.31, J3.33

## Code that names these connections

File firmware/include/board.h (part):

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extern const gpio_pin_t PIN_FDD5_EN;        /* PE2; v1.0 (A11c): ENUV of the TPS25921A eFuse U28 through R135 10k (R28 100k
                                               pull-down keeps the rail off in reset), v0.x: gate of Q2 */
extern const gpio_pin_t PIN_FDD12_EN;       /* PE3; v1.0: ENUV of U29 through R141 10k, v0.x: gate of Q4 */
extern const gpio_pin_t PIN_FLT5;           /* PF9, v1.0 (A11c): U28 FLT, open drain with R137 10k to +3V3; low = undervoltage,
                                               overvoltage or thermal shutdown - also low while the rail is disabled (ENUV low
                                               counts as undervoltage), so only read while the rail is on. v0.x: unconnected */
extern const gpio_pin_t PIN_FLT12;          /* PF10, v1.0: U29 FLT (R143) */

/* v1.0 stage A11d (docs/Timer_Zuteilung.md): sync sensor, J6 pin 2/4/33, rail voltages, Mac port.
 * All of them are inputs or released outputs until a driver uses them (stage A10). */
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#define BOARD_ID_V05_MV         1650u
#define BOARD_ID_V06_MV         1055u   /* 10k/4.7k, SD NAND instead of the microSD slot */
#define BOARD_ID_V07_MV         595u    /* 10k/2.2k, Apple Disk II port */
#define BOARD_ID_V10_MV         2269u   /* 10k/22k, v1.0: front header, electronic loopback, LAN (rev 10) */

/* ---- QSPI PSRAM (board v0.2): APS6404L 8 MB on OCTOSPIM port 1 ---------- */
#define BOARD_HAS_PSRAM         1
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
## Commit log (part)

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2026-01-17 UFI - Universal Flux Interface
